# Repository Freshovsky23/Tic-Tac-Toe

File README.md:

# Tic-Tac-Toe (Kółko i Krzyżyk) - ESP32 & LCD I2C

An interactive Tic-Tac-Toe game implemented on the **ESP32 microcontroller**, utilizing a **4x4 Matrix Keypad** for player input and a **20x4 LCD Display (I2C)** for the visual board representation.

## 📺 Project Demonstration
See the project in action on YouTube:
👉 [Watch the Video Demonstration](https://youtube.com/shorts/P2gXw24iPWE)

---

## 🛠️ Hardware Requirements
* **Microcontroller:** ESP32 (e.g., ESP32 NodeMCU-32S)
* **Display:** LCD 20x4 with an I2C interface adapter (PCF8574)
* **Input:** 4x4 Membrane Matrix Keypad
* **Custom Baseboard PCB** (or Connecting Wires & Breadboard)

### Pin Mapping

#### ⌨️ 4x4 Keypad Connection
| Keypad Pin | ESP32 GPIO |
|------------|------------|
| Row 1      | GPIO 13    |
| Row 2      | GPIO 14    |
| Row 3      | GPIO 27    |
| Row 4      | GPIO 26    |
| Column 1   | GPIO 25    |
| Column 2   | GPIO 33    |
| Column 3   | GPIO 32    |
| Column 4   | GPIO 17    |

#### 📺 LCD 20x4 I2C Connection
| LCD I2C Pin | ESP32 GPIO |
|-------------|------------|
| VCC         | 3.3V (VIN)   |
| GND         | GND        |
| SDA         | GPIO 21    |
| SCL         | GPIO 22    |

---

## 🗺️ Custom PCB Design

To eliminate messy breadboard wiring and create a durable, standalone gaming device, a dedicated dual-layer custom PCB baseboard was designed using **KiCad**. 

### Features:
* **Socketed MCU:** The board utilizes female pin headers, allowing the ESP32 NodeMCU to be easily plugged in or removed.
* **Clean Peripherals Connection:** Dedicated `1x08` and `1x04` pin headers are placed near the edges for straightforward ribbon cable routing from the keypad and LCD.
* **Optimized Power Delivery:** Safe 5V routing directly to the LCD backpack to ensure clear screen contrast without stressing the ESP32's internal 3.3V regulator.
* **Ground Plane:** Full top and bottom copper pour for noise reduction and stable operation.

The complete KiCad design files can be found in the [`hardware/`](./hardware) directory.

### 🖼️ 3D Render Preview:

---

## 🕹️ Game Rules & Controls
1. **Starting the Game:** The game boots up automatically with player **'X'** making the first move.
2. **Making a Move:** Use numeric keys **1 to 9** on the keypad to select a position on the 3x3 grid:
   ```text
   1 | 2 | 3
   ---------
   4 | 5 | 6
   ---------
   7 | 8 | 9

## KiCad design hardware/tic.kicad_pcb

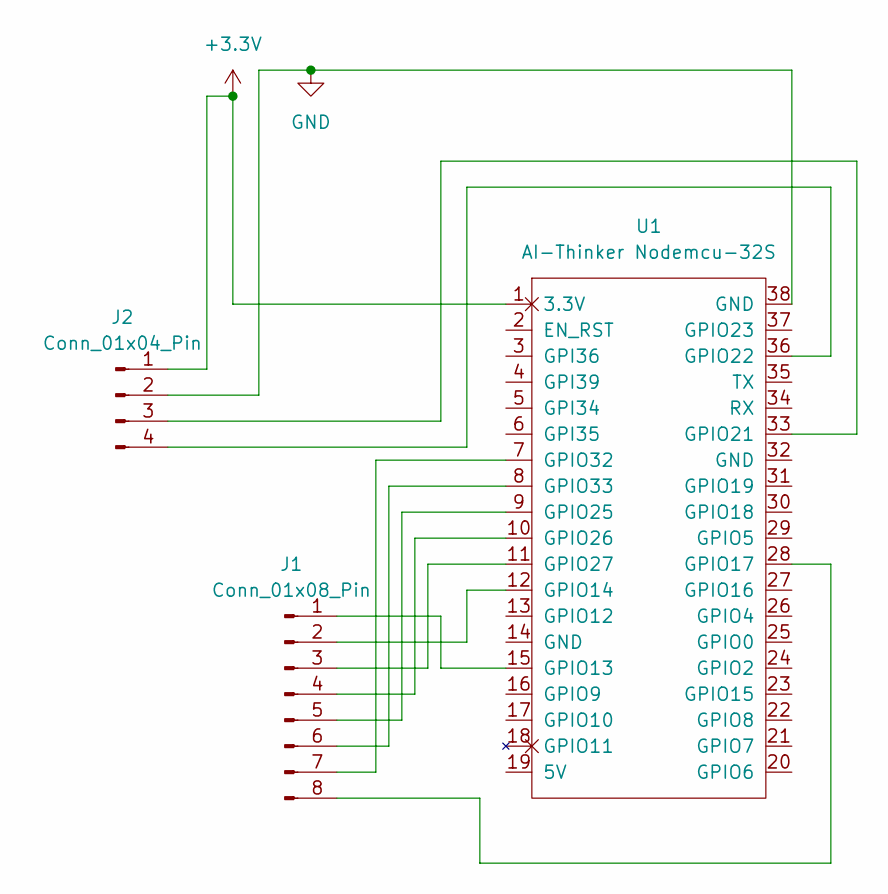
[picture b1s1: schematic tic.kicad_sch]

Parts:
J1: Conn_01x08_Pin; PinHeader_1x08_P2.54mm_Vertical
J2: Conn_01x04_Pin; PinHeader_1x04_P2.54mm_Vertical
U1: AI-Thinker Nodemcu-32S; ai-thinker nodemcu-32s

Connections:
+3.3V: J2.1, U1.1 (3.3V)
GND: J2.2, U1.38 (GND)
unnamed: J1.1, U1.15 (GPIO13)
unnamed: J1.2, U1.12 (GPIO14)
unnamed: J1.3, U1.11 (GPIO27)
unnamed: J1.4, U1.10 (GPIO26)
unnamed: J1.5, U1.9 (GPIO25)
unnamed: J1.6, U1.8 (GPIO33)
unnamed: J1.7, U1.7 (GPIO32)
unnamed: J1.8, U1.28 (GPIO17)
unnamed: J2.3, U1.33 (GPIO21)
unnamed: J2.4, U1.36 (GPIO22)

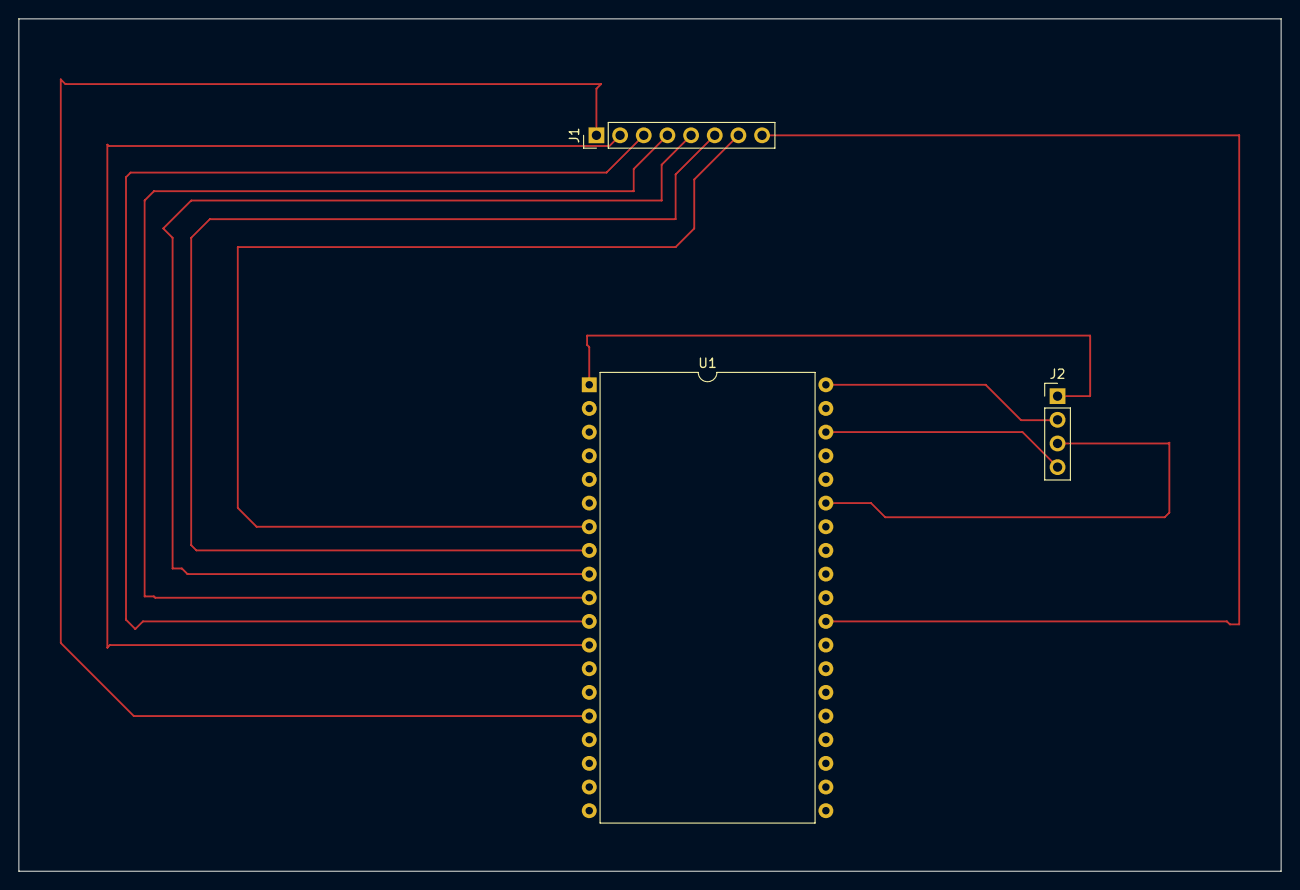
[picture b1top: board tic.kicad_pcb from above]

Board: 2 copper layers, 135.5 x 91.5 mm, 3 parts (0 on the bottom side), 12 nets.

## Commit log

2026-06-06 Initial commit: Add documented code, README and gitignore
2026-06-06 Update VCC voltage for LCD I2C connection
2026-06-06 Dodano projekt PCB w KiCadzie z renderem 3D
2026-06-06 Dodano brakujący render 3D płytki
2026-06-06 Revise README with hardware details and PCB info
    Updated hardware requirements and added custom PCB design section.
